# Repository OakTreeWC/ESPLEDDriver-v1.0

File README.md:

# ESPLEDDriver-v1.0 (In Progress)
ESPLEDDriver is an ESP Powered LED Driver Board for both Addressable and Non-Addressable LEDS. It features a ESP32-WROOM, with either a built in antenna or u.fl port, as well as 4 mosfet channels for powering monochrome and multicolor leds. 
All GPIO pins are exposed directly to the IO headers on the right side, and all power/led related IO can be found on the left side via the screw terminals.
Components have been sized accordingly to support 5-30V input, and up to 5 amps of current draw.

## Firmware
Due to the PD complexity of adding a USBC port to this project, I refrained from adding one. However, that does mean that programming the board requires using a USB to UART adapter.

In terms of firmware to be run on this, I will be using WLED, but ESPHome or any other ESP based software can be used to control it as well.

## Usage
This can be used in multiple ways, but what I believe is the most interesting (and fun) way to do it is to just integrate it with [Home Assistant](https://www.home-assistant.io/). If you really wanted to though, you could just use the Web Interface of WLED, or make your own firmware with its own API or something. The possibilities are literally endless, which is what makes the ESP platform so great.

## I/O
|Pin Number|Function|
|----------|--------|
|0|Addressable LED Data Line|
|4|Non-Addressable LED Channel 1/Red|
|5|Non-Addressable LED Channel 2/Green|
|6|Non-Addressable LED Channel 3/Blue|
|7|Non-Addressable LED Channel 4/White|

All other non-strapping pins are just free, so one may use them for any other purpose.

## Example Wiring Diagrams

## PCB

## Bill Of Materials
|Item                       |Description                                                                                                   |Qty.|Unit Price (USD)|Total Price  (USD)|URL                                                                                                                                                                                                                                                                                                                                                                                                                                                                                                                    |Running Total (USD incl. tax)|
|---------------------------|--------------------------------------------------------------------------------------------------------------|----|----------------|------------------|-----------------------------------------------------------------------------------------------------------------------------------------------------------------------------------------------------------------------------------------------------------------------------------------------------------------------------------------------------------------------------------------------------------------------------------------------------------------------------------------------------------------------|-----------------------------|
|ESP32-C3-WROOM-02U         |ESP32 RF TXRX MOD BLUETOOTH U.FL SMD                                                                          |1   |$3.71           |$3.71             |https://www.digikey.com/en/products/detail/espressif-systems/ESP32-C3-WROOM-02U-N4/15222540                                                                                                                                                                                                                                                                                                                                                                                                                            |$3.71                        |
|277-1580-ND                |5POS Terminal Block, Side Entry, 5mm                                                                          |1   |$1.28           |$1.28             |https://www.digikey.com/en/products/detail/phoenix-contact/1935190/568617                                                                                                                                                                                                                                                                                                                                                                                                                                              |$4.99                        |
|277-1578-ND                |3POS Terminal Block, Side Entry, 5mm                                                                          |1   |$0.72           |$0.72             |https://www.digikey.com/en/products/detail/phoenix-contact/1935174/568615                                                                                                                                                                                                                                                                                                                                                                                                                                              |$5.71                        |
|277-1667-ND                |2POS Terminal Block, Side Entry, 5mm                                                                          |1   |$0.53           |$0.53             |https://www.digikey.com/en/products/detail/phoenix-contact/1935161/568614                                                                                                                                                                                                                                                                                                                                                                                                                                              |$6.24                        |
|IRLR2705PBFCT-ND           |MOSFET N-CH 55V 28A DPAK                                                                                      |10  |$0.58           |$5.76             |https://www.digikey.com/en/products/detail/infineon-technologies/IRLR2705TRPBF/812649                                                                                                                                                                                                                                                                                                                                                                                                                                  |$12.00                       |
|776-MAF95310-ND            |185mm UFL Antenna                                                                                             |1   |$1.13           |$1.13             |https://www.digikey.com/en/products/detail/ezurio/MAF95310/5876486                                                                                                                                                                                                                                                                                                                                                                                                                                                     |$13.13                       |
|311-330HRCT-ND             |RES 330 OHM 1% 1/10W 0603                                                                                     |10  |$0.025          |$0.25             |https://www.digikey.com/en/products/detail/yageo/RC0603FR-07330RL/727162                                                                                                                                                                                                                                                                                                                                                                                                                                               |$13.38                       |
|RNCP0603FTD10K0CT-ND       |RES 10K OHM 1% 1/8W 0603                                                                                      |10  |$0.01           |$0.12             |https://www.digikey.com/en/products/detail/stackpole-electronics-inc/RNCP0603FTD10K0/2240139                                                                                                                                                                                                                                                                                                                                                                                                                           |$13.50                       |
|5272-XL1509-3.3-EVCT-ND    |XL1509 IC REG BUCK 3.3V 3A 8SOP                                                                               |1   |$0.93           |$0.93             |https://www.digikey.com/en/products/detail/evvo/XL1509-3-3-EV/24370104                                                                                                                                                                                                                                                                                                                                                                                                                                                 |$14.43                       |
|4878-SK34SMA-3GCT-ND       |DIODE SCHOTTKY 40V 3A SMA                                                                                     |1   |$0.35           |$0.35             |https://www.digikey.com/en/products/detail/diotec-semiconductor/SK34SMA-3G/13155211                                                                                                                                                                                                                                                                                                                                                                                                                                    |$14.78                       |
|P16479CT-ND                |CAP ALUM POLY 180UF 20% 16V SMD                                                                               |1   |$1.55           |$1.55             |https://www.digikey.com/en/products/detail/panasonic-industry/16SVPF180M/4204811                                                                                                                                                                                                                                                                                                                                                                                                                                       |$16.33                       |
|1276-1860-1-ND             |CAP CER 1UF 50V X5R 0603                                                                                      |10  |$0.08           |$0.80             |https://www.digikey.com/en/products/detail/samsung-electro-mechanics/CL10A105KB8NNNC/3887518                                                                                                                                                                                                                                                                                                                                                                                                                           |$17.13                       |
|36-3568-ND                 |FUSE HOLDER BLADE 500V 30A PCB                                                                                |1   |$1.31           |$1.31             |https://www.digikey.com/en/products/detail/keystone-electronics/3568/2137306                                                                                                                                                                                                                                                                                                                                                                                                                                           |$18.44                       |
|493-1111-ND                |CAP ALUM 1000UF 20% 50V RADIAL                                                                                |1   |$1.30           |$1.30             |https://www.digikey.com/en/products/detail/nichicon/UVR1H102MHD/588852                                                                                                                                                                                                                                                                                                                                                                                                                                                 |$19.74                       |
|SMBJ30ALFCT-ND             |TVS DIODE 30VWM 48.4VC DO214AA                                                                                |1   |$0.50           |$0.50             |https://www.digikey.com/en/products/detail/littelfuse-inc/SMBJ30A/286004                                                                                                                                                                                                                                                                                                                                                                                                                                               |$20.24                       |
|SRR1210A-680MCT-ND         |FIXED IND 68UH 3A 102 MOHM SMD                                                                                |1   |$1.47           |$1.47             |https://www.digikey.com/en/products/detail/bourns-inc/SRR1210A-680M/5031009                                                                                                                                                                                                                                                                                                                                                                                                                                            |$21.71                       |
|399-A768MS107M1HLAE024CT-ND|CAP ALUM POLY 100UF 20% 50V SMD                                                                               |1   |$1.22           |$1.22             |https://www.digikey.com/en/products/detail/kemet/A768MS107M1HLAE024/12704540                                                                                                                                                                                                                                                                                                                                                                                                                                           |$22.93                       |
|Female IO Headers          |20PCS Single Row Straight Female Pin Socket Pin Header Connector Pin Strip 2.54mm Spacing for PCB Board Shield|1   |$5.99           |$5.99             |https://www.amazon.com/Ferwooh-Single-Straight-Connector-Spacing/dp/B0CZ6X313F/ref=sr_1_2?crid=39VMGF4CCA1GG&dib=eyJ2IjoiMSJ9.NBa46IPaB8xWVTMRTULFOi3t2_Bh3ctx1FmyruNSGoGmYMdxk0LClbzoKFV-c0LT81RXjUFz13WOxkmCkKyU9QgRG8rwSUfN6dJtCpupQRfLCY0_F6_al_UNWfSwz9q3z1k9db4CpDrOTnL1TruZ9XrdwOYw0u1U0dscYfxgbU-Gp83MaORzWl8d61gyXKhzst-xlNGDYB-oXc_l3OwoJDj05kOEF4lXotFBnQoTlWQ.HyzfQy6889qkZPpNsp2jaawJgTKnZesUPEsDKpRi2kk&dib_tag=se&keywords=gpio+header+female&qid=1789867484&sprefix=gpio+header+fema%2Caps%2C180&sr=8-2|$28.92                       |
|450-1650-ND                |SWITCH TACTILE SPST-NO 0.05A 24V                                                                              |2   |$0.13           |$0.26             |https://www.digikey.com/en/products/detail/te-connectivity-alcoswitch-switches/1825910-6/1632536                                                                                                                                                                                                                                                                                                                                                                                                                       |$29.18                       |
|F989-ND                    |FUSE AUTOMOTIVE 5A 32VDC BLADE                                                                                |2   |$0.39           |$0.78             |https://www.digikey.com/en/products/detail/littelfuse-inc/0297005-WXNV/146583                                                                                                                                                                                                                                                                                                                                                                                                                                          |$29.96                       |
|Digikey Shipping           |                                                                                                              |1   |$4.99           |$4.99             |                                                                                                                                                                                                                                                                                                                                                                                                                                                                                                                       |$34.95                       |
|Digikey Tariffs            |                                                                                                              |1   |$4.71           |$4.71             |                                                                                                                                                                                                                                                                                                                                                                                                                                                                                                                       |$39.66                       |
|PCB                        |From JLCPCB                                                                                                   |1   |$4.00           |$4.00             |                                                                                                                                                                                                                                                                                                                                                                                                                                                                                                                       |$43.66                       |
|JLC Shipping               |                                                                                                              |1   |$6.77           |$6.77             |                                                                                                                                                                                                                                                                                                                                                                                                                                                                                                                       |$50.43                       |
|Digikey TAX                |                                                                                                              |1   |$2.80           |$2.80             |                                                                                                                                                                                                                                                                                                                                                                                                                                                                                                                       |$53.23                       |
|Amazon TAX                 |                                                                                                              |1   |$0.63           |$0.63             |                                                                                                                                                                                                                                                                                                                                                                                                                                                                                                                       |$53.86                       |

## AI Usage Declaration
AI was used in the making of this project, in component research, schematic/pcb verification, general sanity checks, as well as some copilot commit notes (for readme)

## Gallery

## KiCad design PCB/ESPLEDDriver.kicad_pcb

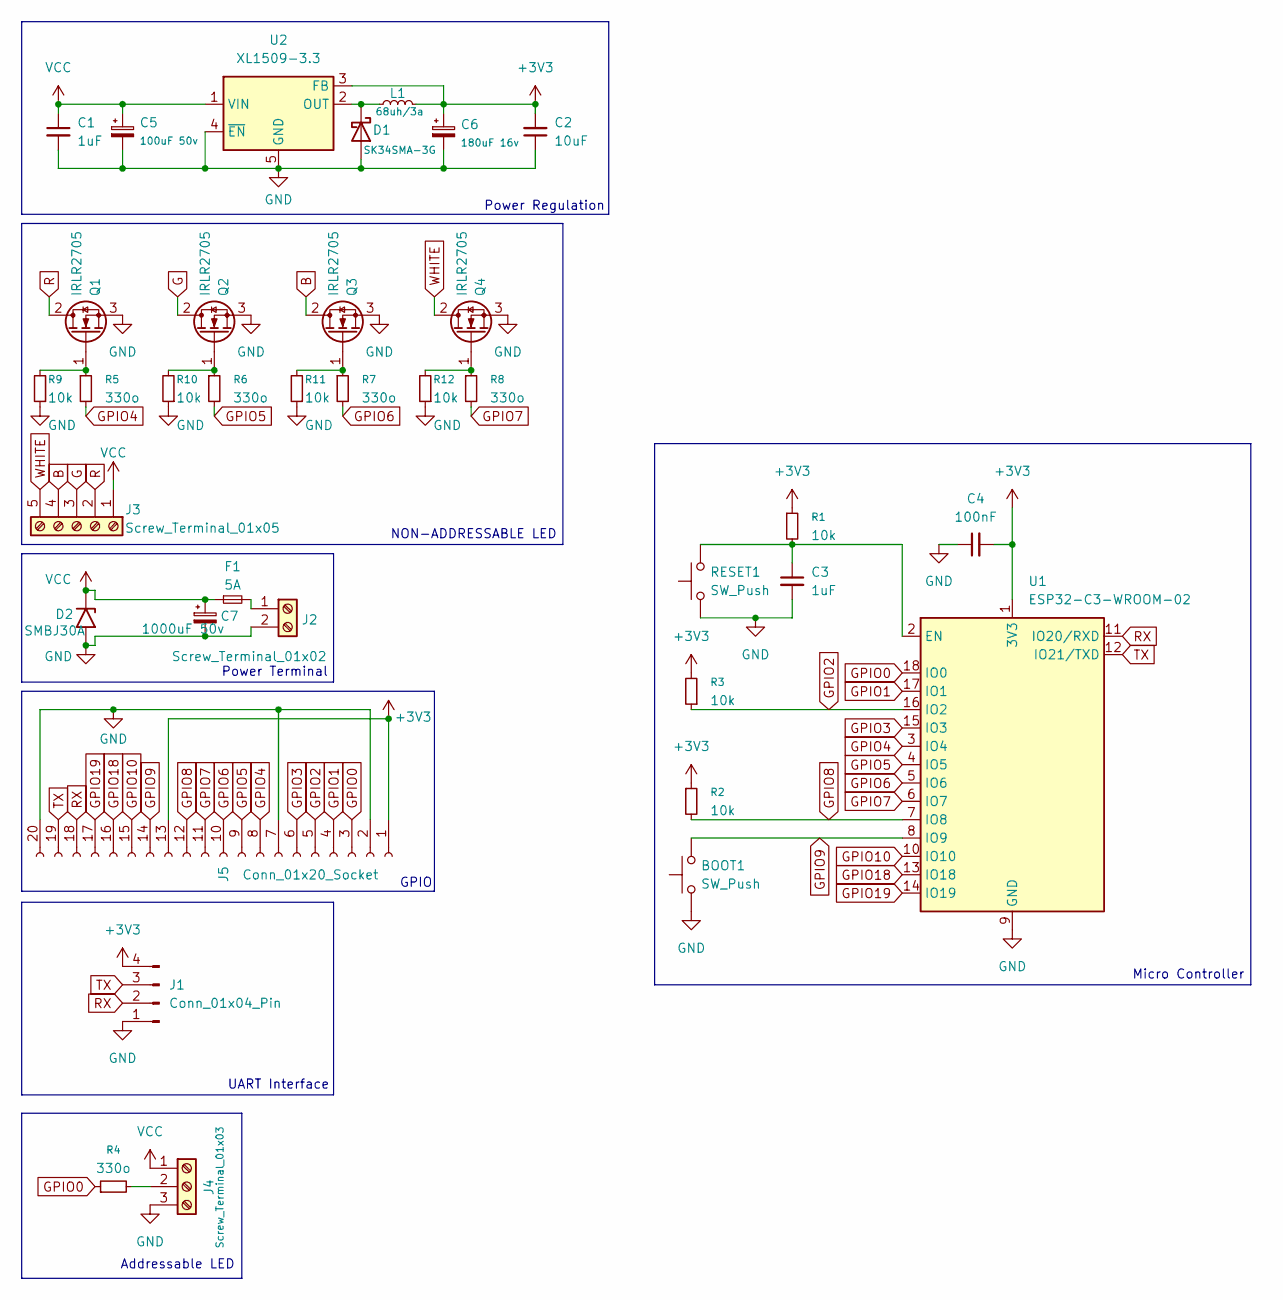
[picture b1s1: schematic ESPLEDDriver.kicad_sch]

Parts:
BOOT1: SW_Push; SW_PUSH_6mm
C1, C3: 1uF; C_0603_1608Metric_Pad1.08x0.95mm_HandSolder
C2: 10uF; C_0603_1608Metric_Pad1.08x0.95mm_HandSolder
C4: 100nF; C_0603_1608Metric_Pad1.08x0.95mm_HandSolder
C5: 100uF 50v; CP_Elec_10x10
C6: 180uF 16v; CP_Elec_6.3x5.9
C7: 1000uF 50v; CP_Radial_D12.5mm_P5.00mm
D1: SK34SMA-3G; D_SMA_Handsoldering
D2: SMBJ30A; D_SMB
F1: 5A; FUSE_3568
J1: Conn_01x04_Pin; PinHeader_1x04_P2.54mm_Vertical
J2: Screw_Terminal_01x02; TerminalBlock_Phoenix_PT-1,5-2-5.0-H_1x02_P5.00mm_Horizontal
J3: Screw_Terminal_01x05; TerminalBlock_Phoenix_PT-1,5-5-5.0-H_1x05_P5.00mm_Horizontal
J4: Screw_Terminal_01x03; TerminalBlock_Phoenix_PT-1,5-3-5.0-H_1x03_P5.00mm_Horizontal
J5: Conn_01x20_Socket; PinSocket_1x20_P2.54mm_Vertical
L1: 68uh/3a; L_Bourns_SRR1210A
Q1, Q2, Q3, Q4: IRLR2705; TO-252-2
R1, R2, R3, R9, R10, R11, R12: 10k; R_0603_1608Metric_Pad0.98x0.95mm_HandSolder
R4, R5, R6, R7, R8: 330o; R_0603_1608Metric_Pad0.98x0.95mm_HandSolder
RESET1: SW_Push; SW_PUSH_6mm
U1: ESP32-C3-WROOM-02
U2: XL1509-3.3; SOIC-8_3.9x4.9mm_P1.27mm

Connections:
+3V3: C2.2, C4.2, C6.1, J1.4, J5.1, J5.13, L1.2, R1.1, R2.1, R3.2, U1.1 (3V3), U2.3 (FB)
B: J3.4, Q3.2 (D)
G: J3.3, Q2.2 (D)
GND: BOOT1.1, C1.2, C2.1, C3.2, C4.1, C5.2, C6.2, C7.2, D1.2 (A), D2.2 (A2), J1.1, J2.2, J4.3, J5.2, J5.7, J5.20, Q1.3 (S), Q2.3 (S), Q3.3 (S), Q4.3 (S), R9.1, R10.1, R11.1, R12.1, RESET1.1, U1.9 (GND), U1.19 (GND), U2.4 (~EN), U2.5 (GND), U2.6 (GND), U2.7 (GND), U2.8 (GND)
GPIO0: J5.3, R4.1, U1.18 (IO0)
GPIO1: J5.4, U1.17 (IO1)
GPIO2: J5.5, R3.1, U1.16 (IO2)
GPIO3: J5.6, U1.15 (IO3)
GPIO4: J5.8, R5.2, U1.3 (IO4)
GPIO5: J5.9, R6.2, U1.4 (IO5)
GPIO6: J5.10, R7.2, U1.5 (IO6)
GPIO7: J5.11, R8.2, U1.6 (IO7)
GPIO8: J5.12, R2.2, U1.7 (IO8)
GPIO9: BOOT1.2, J5.14, U1.8 (IO9)
GPIO10: J5.15, U1.10 (IO10)
GPIO18: J5.16, U1.13 (IO18)
GPIO19: J5.17, U1.14 (IO19)
unnamed: D1.1 (K), L1.1, U2.2 (OUT)
unnamed: F1.2, F1.4, J2.1
unnamed: J4.2, R4.2
unnamed: Q1.1 (G), R5.1, R9.2
unnamed: Q2.1 (G), R6.1, R10.2
unnamed: Q3.1 (G), R7.1, R11.2
unnamed: Q4.1 (G), R8.1, R12.2
unnamed: C3.1, R1.2, RESET1.2, U1.2 (EN)
R: J3.2, Q1.2 (D)
RX: J1.2, J5.18, U1.11 (IO20/RXD)
TX: J1.3, J5.19, U1.12 (IO21/TXD)
VCC: C1.1, C5.1, C7.1, D2.1 (A1), F1.1, F1.3, J3.1, J4.1, U2.1 (VIN)
WHITE: J3.5, Q4.2 (D)

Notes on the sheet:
NON-ADDRESSABLE LED
UART Interface
GPIO
Power Regulation
Micro Controller
Addressable LED
Power Terminal

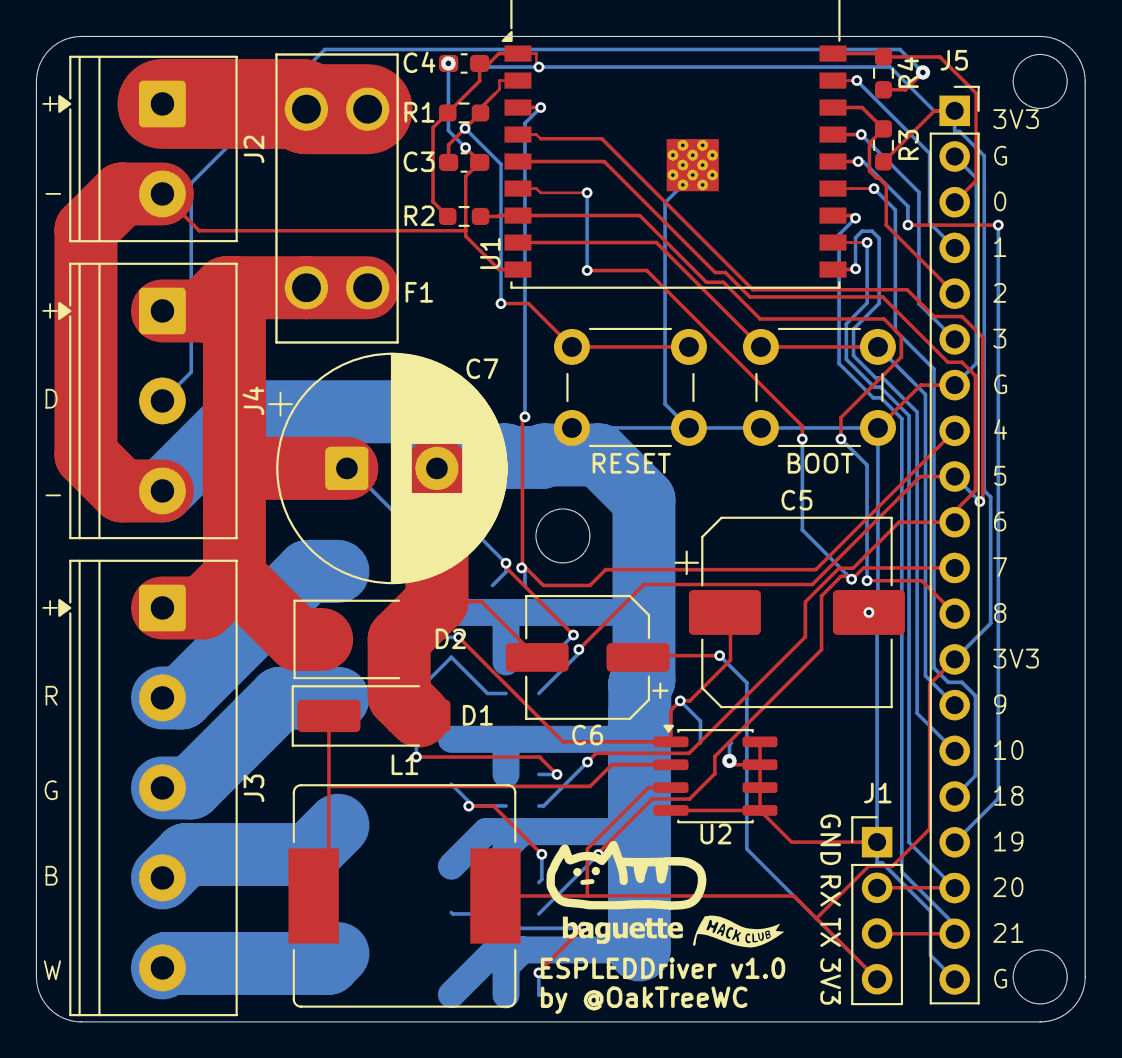
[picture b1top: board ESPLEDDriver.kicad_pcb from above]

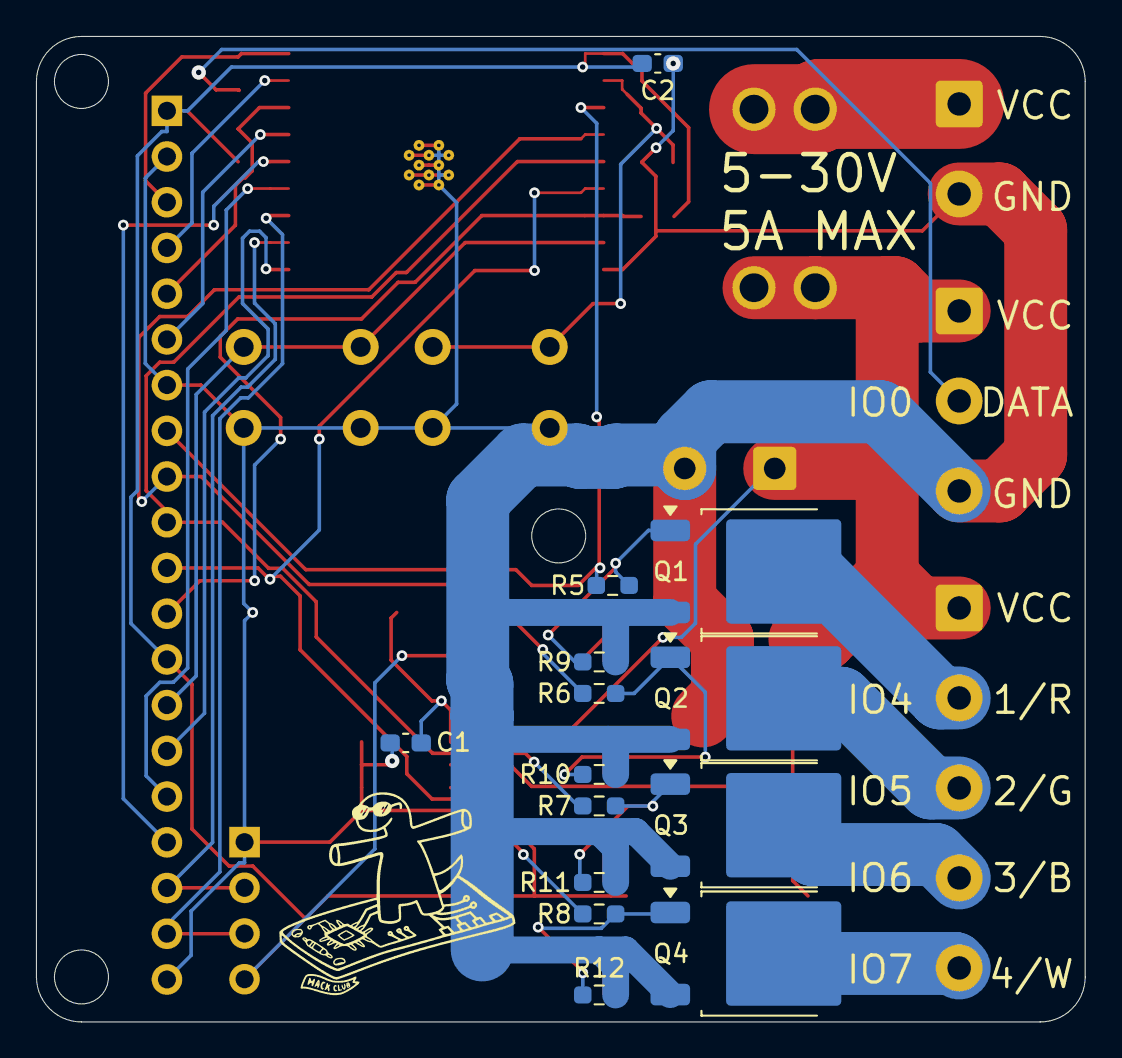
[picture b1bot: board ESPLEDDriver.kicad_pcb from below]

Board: 2 copper layers, 58.3 x 54.8 mm, 36 parts (14 on the bottom side), 30 nets.
